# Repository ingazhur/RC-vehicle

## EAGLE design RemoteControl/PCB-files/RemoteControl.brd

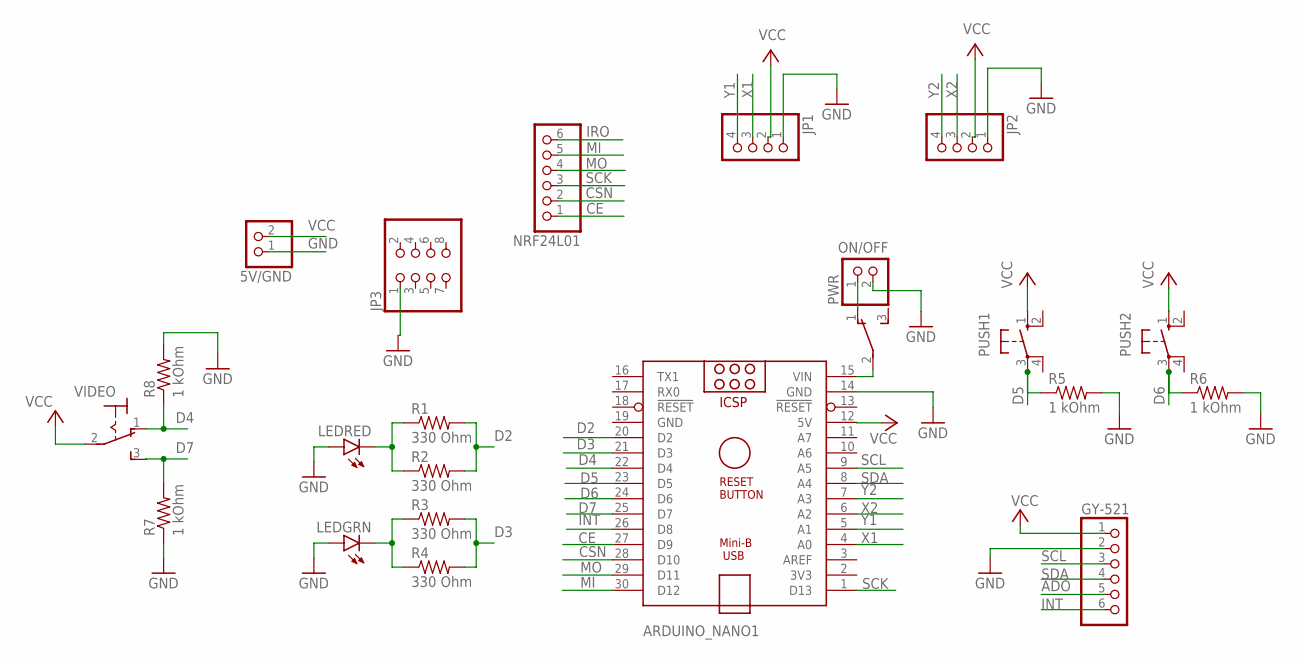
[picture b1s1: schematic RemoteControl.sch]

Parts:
5V/GND: PINHD-1X2; 1X02
ARDUINO_NANO1: ARDUINO_NANO
GY-521: PINHD-1X6; 1X06
JP1, JP2: PINHD-1X4; 1X04
JP3: PINHD-2X4; 2X04
LEDGRN: LED5MM
LEDRED: LED5MM
NRF24L01: PINHD-1X6; 1X06
ON/OFF: TL36WO; TL3XWO
PUSH1, PUSH2: 10-XX; B3F-10XX
PWR: PINHD-1X2; 1X02
R1, R2, R3, R4: 330 Ohm; 0204/7
R5, R6, R7, R8: 1 kOhm; 0204/7
VIDEO: 320-916

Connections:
ADO: GY-521.5
CE: ARDUINO_NANO1.27 (D9), NRF24L01.1
CSN: ARDUINO_NANO1.28 (D10), NRF24L01.2
D2: ARDUINO_NANO1.20 (D2), R1.2, R2.2
D3: ARDUINO_NANO1.21 (D3), R3.2, R4.2
D4: ARDUINO_NANO1.22 (D4), R8.1, VIDEO.1 (O)
D5: ARDUINO_NANO1.23 (D5), PUSH1.3, R5.1
D6: ARDUINO_NANO1.24 (D6), PUSH2.3, R6.1
D7: ARDUINO_NANO1.25 (D7), R7.2, VIDEO.3 (S)
GND: 5V/GND.1, ARDUINO_NANO1.14 (GND), ARDUINO_NANO1.19 (GND), GY-521.2, JP1.1, JP2.1, JP3.1, LEDGRN.A, LEDRED.A, PWR.2, R5.2, R6.2, R7.1, R8.2
INT: ARDUINO_NANO1.26 (D8), GY-521.6
IRO: NRF24L01.6
MI: ARDUINO_NANO1.30 (D12), NRF24L01.5
MO: ARDUINO_NANO1.29 (D11), NRF24L01.4
unnamed: ARDUINO_NANO1.15 (VIN), ON/OFF.2
unnamed: ON/OFF.1 (O), PWR.1
unnamed: LEDRED.K (C), R1.1, R2.1
unnamed: LEDGRN.K (C), R3.1, R4.1
SCK: ARDUINO_NANO1.1 (D13), NRF24L01.3
SCL: ARDUINO_NANO1.9 (A5), GY-521.3
SDA: ARDUINO_NANO1.8 (A4), GY-521.4
VCC: 5V/GND.2, ARDUINO_NANO1.12 (5V), GY-521.1, JP1.2, JP2.2, PUSH1.1 (S), PUSH2.1 (S), VIDEO.2
X1: ARDUINO_NANO1.4 (A0), JP1.3
X2: ARDUINO_NANO1.6 (A2), JP2.3
Y1: ARDUINO_NANO1.5 (A1), JP1.4
Y2: ARDUINO_NANO1.7 (A3), JP2.4

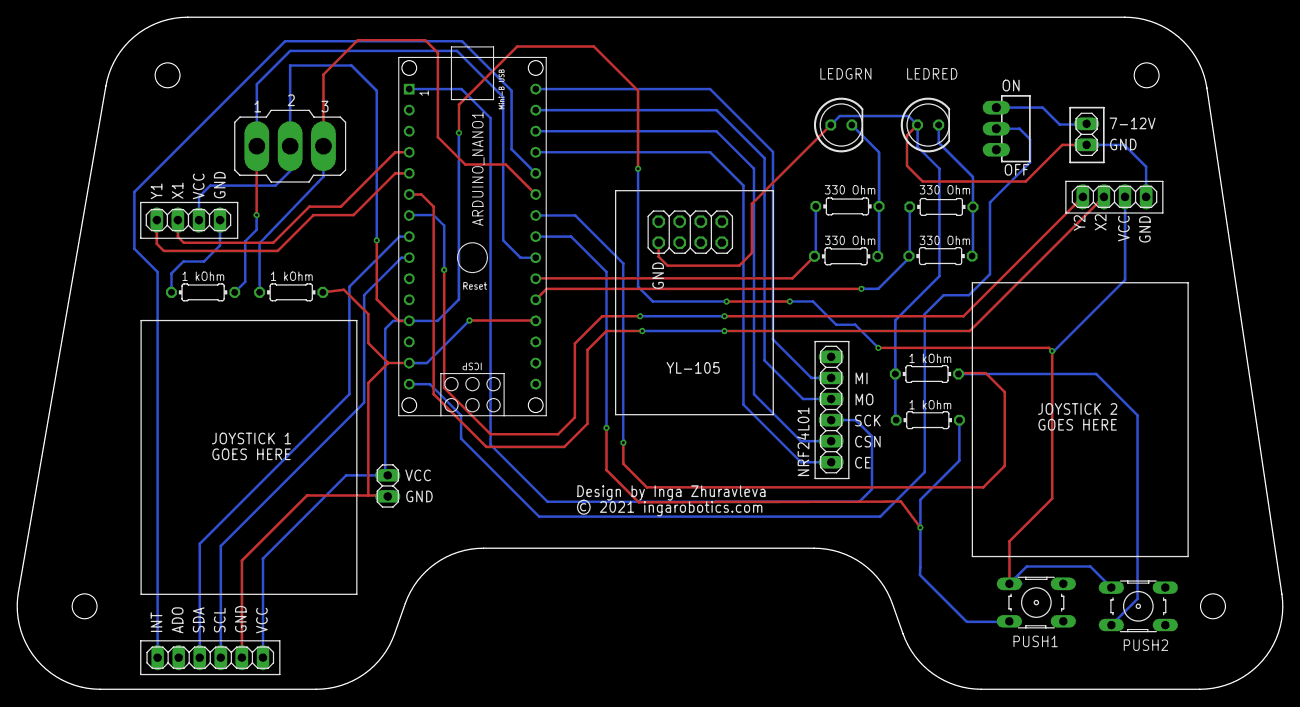
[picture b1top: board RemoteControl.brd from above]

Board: 2 copper layers, 152.5 x 81.0 mm, 22 parts (0 on the bottom side), 24 nets.

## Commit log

2021-01-13 First commit - added PCB files
2021-01-16 Adding files for laser cutting

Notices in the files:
RemoteControl/PCB-files/RemoteControl.brd:
© 2021 ingarobotics.com
